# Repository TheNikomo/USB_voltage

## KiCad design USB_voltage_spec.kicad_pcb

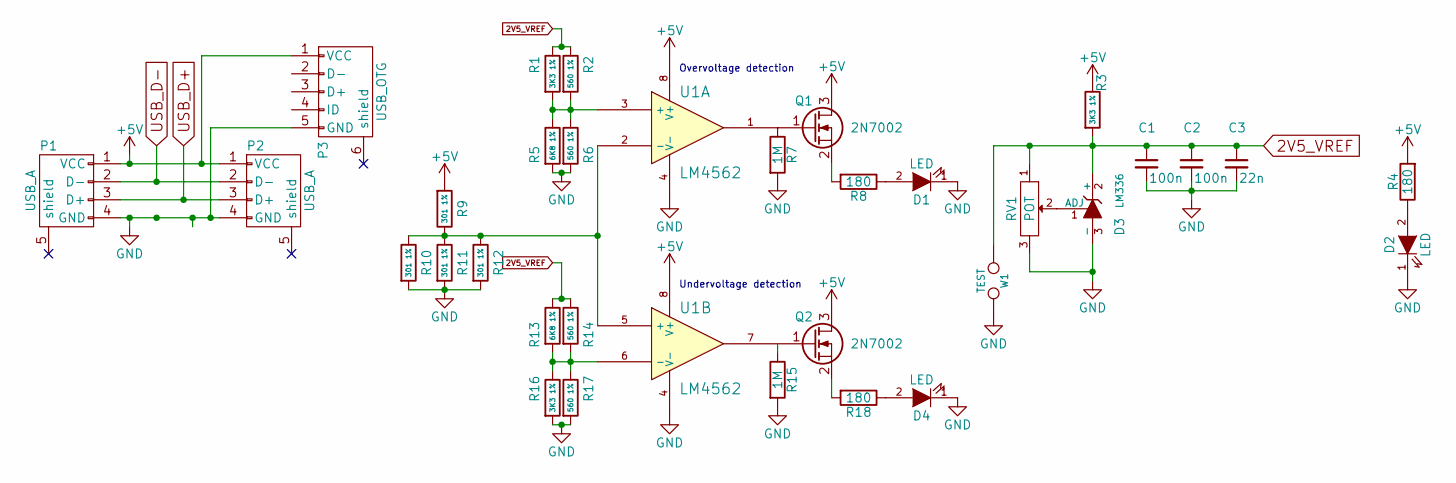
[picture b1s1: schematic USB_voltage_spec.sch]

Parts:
C1, C2: 100n; C_0805
C3: 22n; C_0805
D1, D2, D4: LED; LED-1206
D3: LM336; TO-92_Molded_Narrow
P1, P2: USB_A
P3: USB_OTG; USB_Micro-B_5.5mm
Q1, Q2: 2N7002; SOT23_Transistor_RevA_03Aug2010
R1, R3, R16: 3K3 1%; R_1206
R2, R6, R14, R17: 560 1%; R_1206
R4, R8, R18: 180; R_1206
R5, R13: 6K8 1%; R_1206
R7, R15: 1M; R_1206
R9, R10, R11, R12: 301 1%; R_1206
RV1: POT; Potentiometer_Bourns_3006P_Angular_ScrewFront
U1: LM4562; DIP-8_W7.62mm
W1: TEST; TESTPOINT

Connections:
2V5_VREF: C1.1, C2.1, C3.1, D3.2 (+), R1.1, R2.1, R3.2, R13.1, R14.1, RV1.1, W1.1; also elsewhere on the board
+5V: P1.1 (VCC), P2.1 (VCC), P3.1 (VCC), Q1.3 (D), Q2.3 (D), R3.1, R4.2, R9.2, U1.8 (V+); also elsewhere on the board
GND: C1.2, C2.2, C3.2, D1.1 (K), D2.1 (K), D3.3 (-), D4.1 (K), P1.4 (GND), P2.4 (GND), P3.5 (GND), R5.2, R6.2, R7.2, R10.2, R11.2, R12.2, R15.2, R16.2, R17.2, RV1.3, U1.4 (V-), W1.2; also elsewhere on the board
unnamed: D1.2 (A), R8.1
unnamed: D2.2 (A), R4.1
unnamed: D3.1 (ADJ), RV1.2
unnamed: D4.2 (A), R18.1
unnamed: P1.5 (shield), P2.5 (shield), P3.6 (shield)
unnamed: Q1.1 (G), R7.1, U1.1
unnamed: Q1.2 (S), R8.2
unnamed: Q2.1 (G), R15.1, U1.7
unnamed: Q2.2 (S), R18.2
unnamed: R1.2, R2.2, R5.1, R6.1, U1.3 (+)
unnamed: R9.1, R10.1, R11.1, R12.1, U1.2 (-), U1.5 (+)
unnamed: R13.2, R14.2, R16.1, R17.1, U1.6 (-)
USB_D+: P1.3 (D+), P2.3 (D+)
USB_D-: P1.2 (D-), P2.2 (D-)

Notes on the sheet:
Overvoltage detection
Undervoltage detection

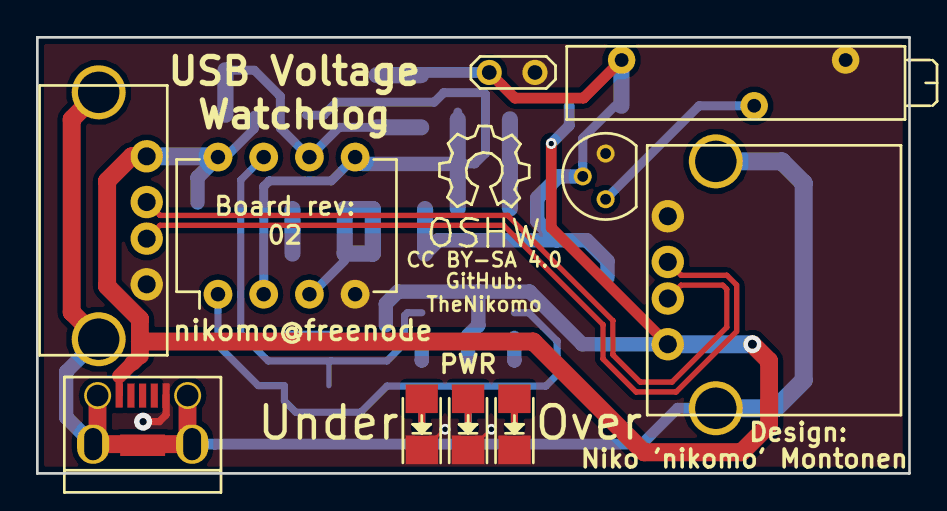
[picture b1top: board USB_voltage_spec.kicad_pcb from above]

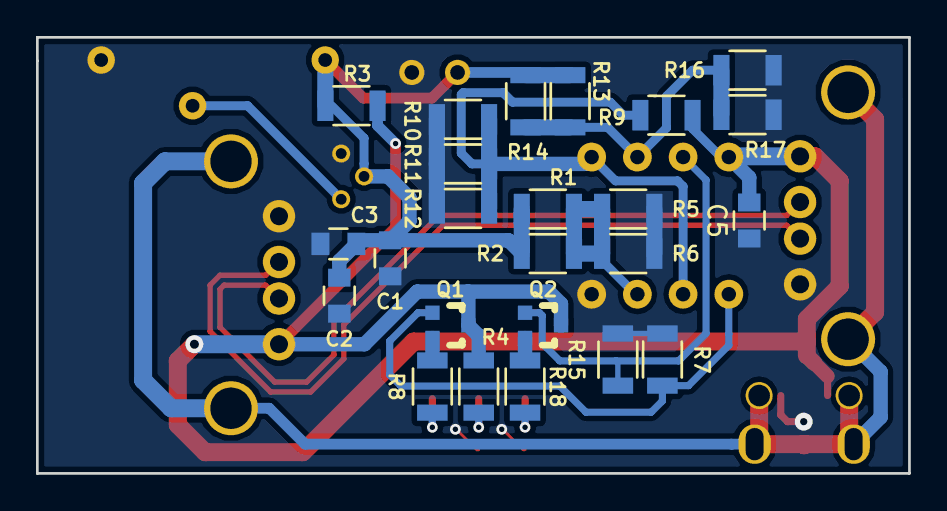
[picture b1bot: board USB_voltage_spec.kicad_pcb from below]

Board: 2 copper layers, 48.4 x 24.2 mm, 34 parts (24 on the bottom side), 17 nets.

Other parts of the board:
2V5 TEST: TESTPOINT
C5: 100n; C_0805

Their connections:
2V5_VREF: 2V5 TEST.1; also elsewhere on the board
+5V: C5.1; also elsewhere on the board
GND: 2V5 TEST.2, C5.2; also elsewhere on the board

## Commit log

2015-12-18 Initial, and probably last, commit
2015-12-18 I lied.

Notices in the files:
USB_voltage_spec.kicad_pcb:
CC BY-SA 4.0
